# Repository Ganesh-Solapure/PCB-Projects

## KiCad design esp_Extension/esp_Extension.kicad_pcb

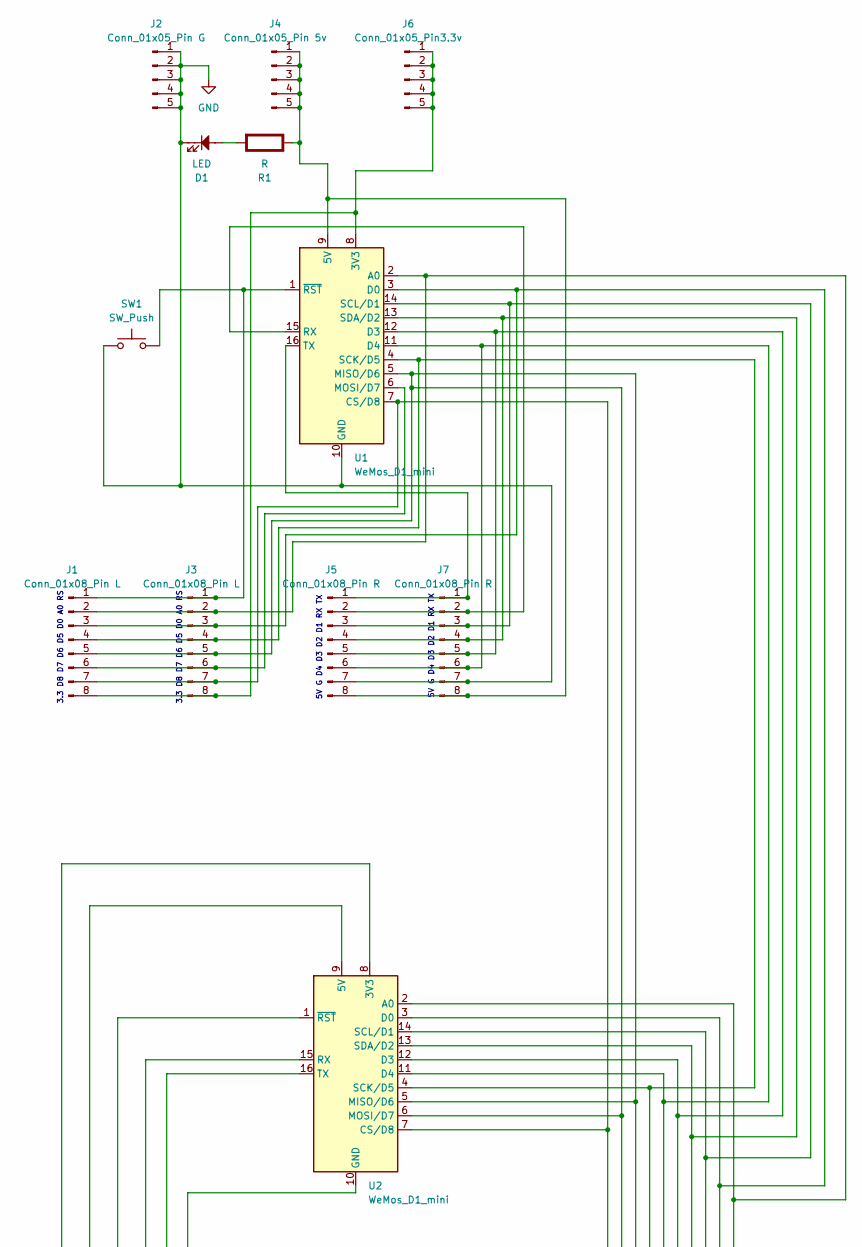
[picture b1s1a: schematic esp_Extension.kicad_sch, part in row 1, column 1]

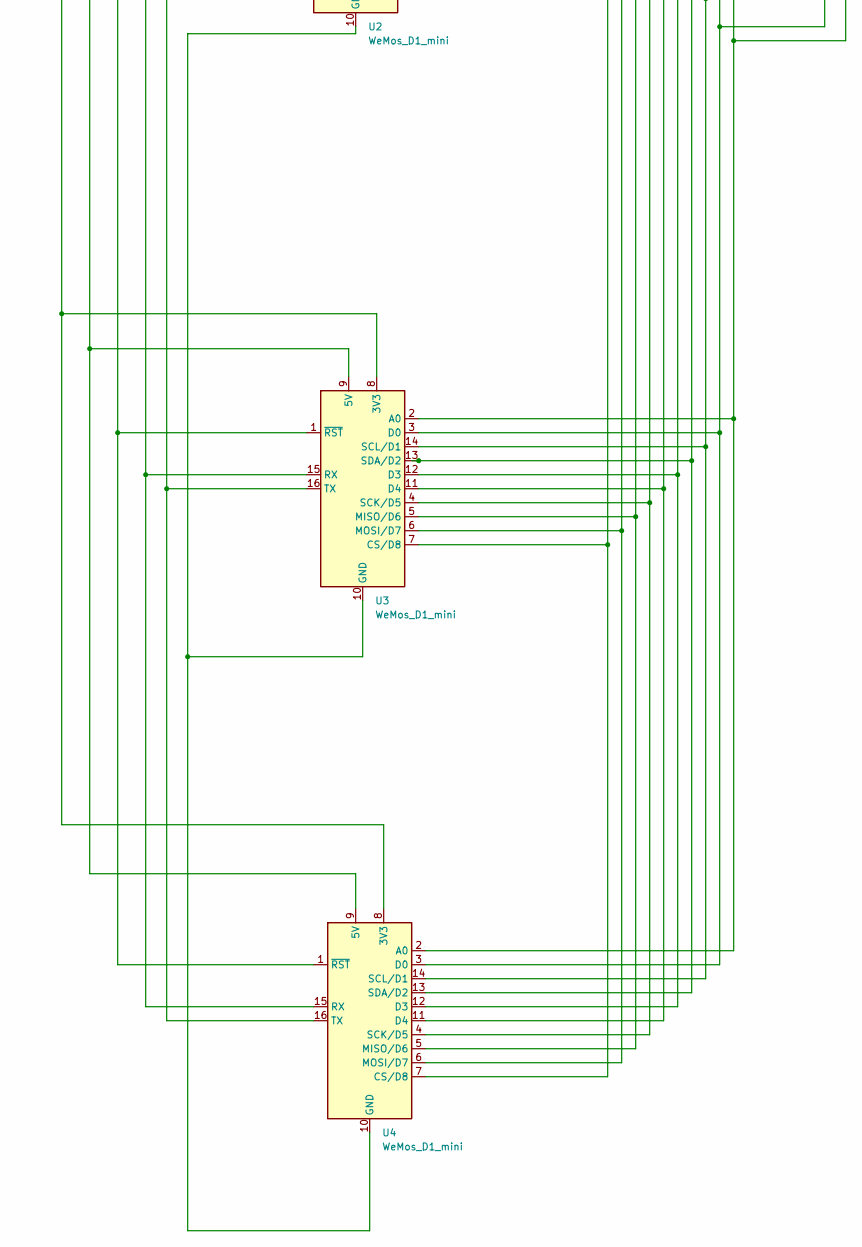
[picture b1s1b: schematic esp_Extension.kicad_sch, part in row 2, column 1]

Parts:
D1: LED; LED_D5.0mm
J1: Conn_01x08_Pin L; PinHeader_1x08_P2.54mm_Vertical
J2: Conn_01x05_Pin G; PinHeader_1x05_P2.54mm_Vertical
J3: Conn_01x08_Pin L; TerminalBlock_RND_205-00018_1x08_P5.00mm_Horizontal
J4: Conn_01x05_Pin 5v; PinHeader_1x05_P2.54mm_Vertical
J5: Conn_01x08_Pin R; TerminalBlock_RND_205-00018_1x08_P5.00mm_Horizontal
J6: Conn_01x05_Pin3.3v; PinHeader_1x05_P2.54mm_Vertical
J7: Conn_01x08_Pin R; PinHeader_1x08_P2.54mm_Vertical
R1: R; R_Axial_DIN0207_L6.3mm_D2.5mm_P7.62mm_Horizontal; Rating W
SW1: SW_Push; SW_PUSH_6mm_H5mm
U1, U2, U3, U4: WeMos_D1_mini; WEMOS_D1_mini_light

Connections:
GND: D1.1, J2.1, J2.2, J2.3, J2.4, J2.5, J5.7, J7.7, SW1.1, U1.10 (GND)
unnamed: J1.1, J3.1, SW1.2, U1.1 (~RST)
unnamed: J1.2, J3.2, U1.2 (A0), U2.2 (A0), U3.2 (A0), U4.2 (A0)
unnamed: J1.3, J3.3, U1.3 (D0), U2.3 (D0), U3.3 (D0), U4.3 (D0)
unnamed: J1.4, J3.4, U1.4 (SCK/D5), U2.4 (SCK/D5), U3.4 (SCK/D5), U4.4 (SCK/D5)
unnamed: J1.5, J3.5, U1.5 (MISO/D6), U2.5 (MISO/D6), U2.6 (MOSI/D7), U3.5 (MISO/D6), U3.6 (MOSI/D7), U4.5 (MISO/D6), U4.6 (MOSI/D7)
unnamed: J1.6, J3.6, U1.6 (MOSI/D7)
unnamed: J1.7, J3.7, U1.7 (CS/D8), U2.7 (CS/D8), U3.7 (CS/D8), U4.7 (CS/D8)
unnamed: J1.8, J3.8, J6.1, J6.2, J6.3, J6.4, J6.5, U1.8 (3V3)
unnamed: J4.1, J4.2, J4.3, J4.4, J4.5, J5.8, J7.8, R1.1 (+), U1.9 (5V)
unnamed: J5.1, J7.1, U1.16 (TX)
unnamed: J5.2, J7.2, U1.15 (RX)
unnamed: J5.3, J7.3, U1.14 (SCL/D1), U2.14 (SCL/D1), U3.14 (SCL/D1), U4.14 (SCL/D1)
unnamed: J5.4, J7.4, U1.13 (SDA/D2), U2.13 (SDA/D2), U3.13 (SDA/D2), U4.13 (SDA/D2)
unnamed: J5.5, J7.5, U1.12 (D3), U2.12 (D3), U3.12 (D3), U4.12 (D3)
unnamed: J5.6, J7.6, U1.11 (D4), U2.11 (D4), U3.11 (D4), U4.11 (D4)
unnamed: D1.2, R1.2 (-)
unnamed: U2.8 (3V3), U3.8 (3V3), U4.8 (3V3)
unnamed: U2.9 (5V), U3.9 (5V), U4.9 (5V)
unnamed: U2.10 (GND), U3.10 (GND), U4.10 (GND)
unnamed: U2.15 (RX), U3.15 (RX), U4.15 (RX)
unnamed: U2.16 (TX), U3.16 (TX), U4.16 (TX)
unnamed: U2.1 (~RST), U3.1 (~RST), U4.1 (~RST)

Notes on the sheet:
5V G D4 D3 D2 D1 RX TX
3.3 D8 D7 D6 D5 D0 A0 RS

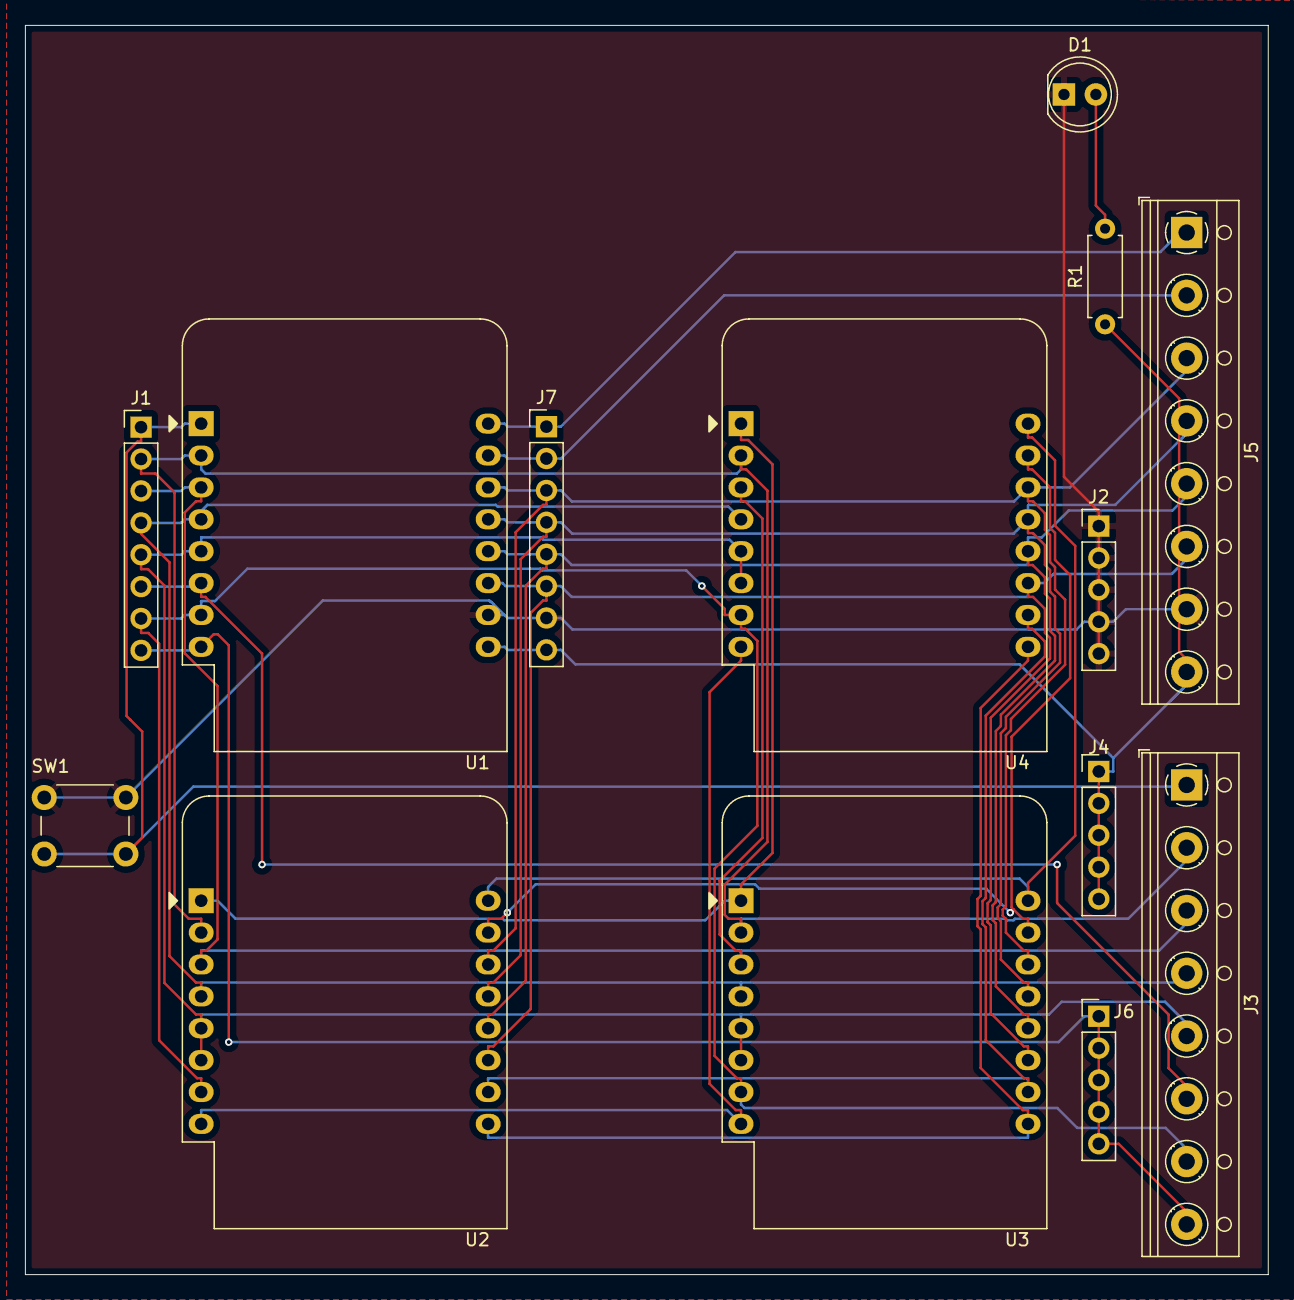
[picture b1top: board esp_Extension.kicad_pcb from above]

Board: 2 copper layers, 99.0 x 99.5 mm, 14 parts (0 on the bottom side), 23 nets.

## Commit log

2024-12-06 init
    6/12/2024
2024-12-10 10 dec
2024-12-11 11 Dec
2024-12-16 done
